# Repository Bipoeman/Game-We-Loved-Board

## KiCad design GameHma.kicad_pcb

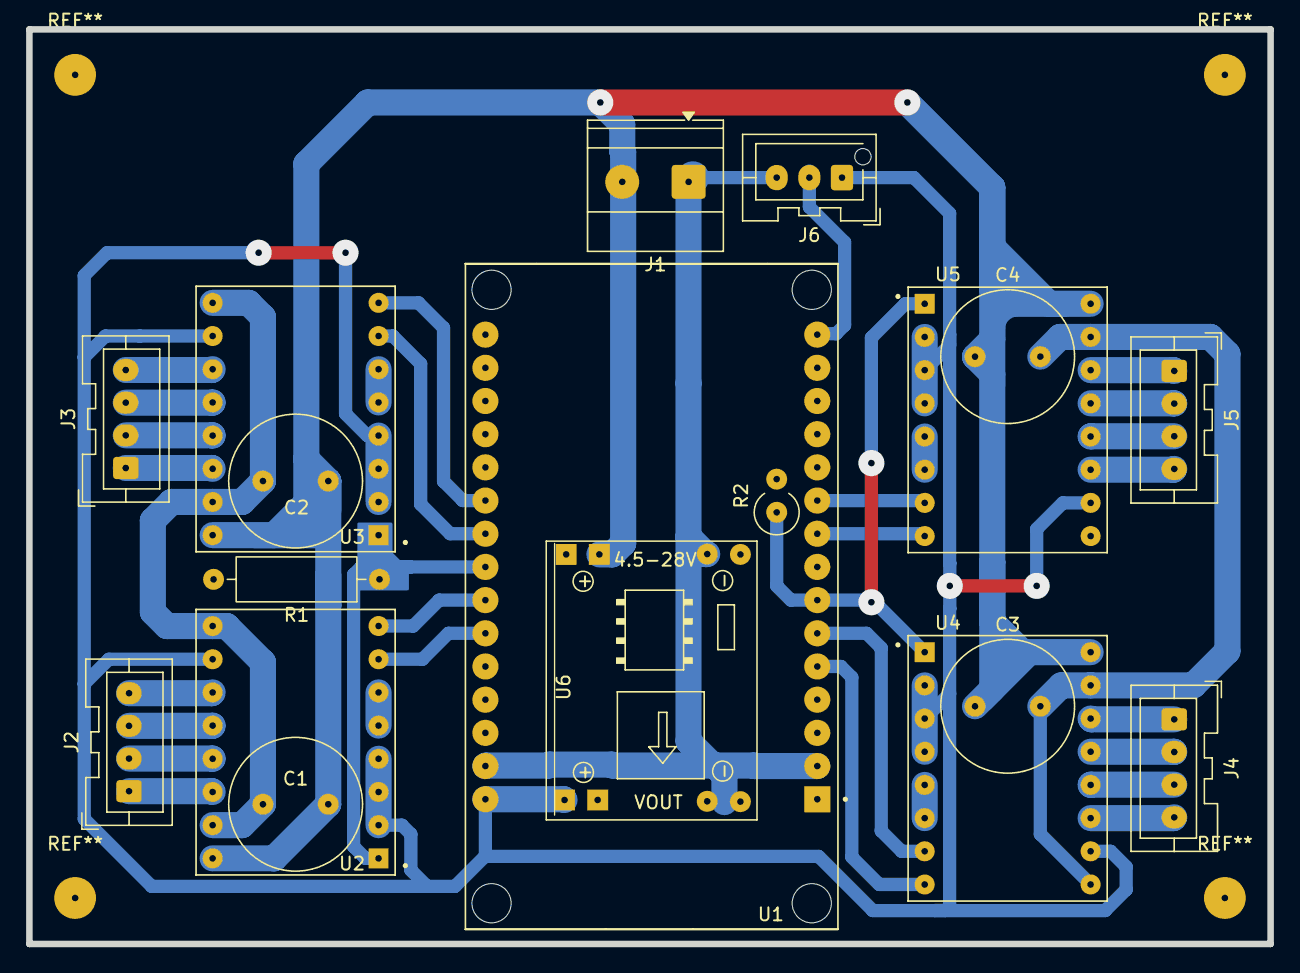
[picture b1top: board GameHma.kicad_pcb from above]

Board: 2 copper layers, 95.0 x 70.0 mm, 18 parts (0 on the bottom side), 34 nets.

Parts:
C1, C2, C3, C4: 100u; C_Radial_D10.0mm_H16.0mm_P5.00mm
J1: Screw_Terminal_01x02; TerminalBlock_Phoenix_MKDS-1,5-2-5.08_1x02_P5.08mm_Horizont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
J2, J3, J4, J5: Motor_Terminal_01x04; JST_XA_B04B-XASK-1_1x04_P2.50mm_Vertical
J6: Conn_01x03; JST_XA_B03B-XASK-1-A_1x03_P2.50mm_Vertical
R1: 10; R_Axial_DIN0309_L9.0mm_D3.2mm_P12.70mm_Horizontal
R2: 10; R_Axial_DIN0309_L9.0mm_D3.2mm_P2.54mm_Vertical
U1: ESP32-DEVKIT-V1; ESP32 Dev Board
U2, U3, U4, U5: A4988 Stepper Driver Module; A4988 Stepper Driver
U6: SRT_MP1584EN; MPT1584EN_Module

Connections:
+V_{DD}: J6.1, U1.30 (VIN), U2.2 (MS1), U2.3 (MS2), U2.4 (MS3), U2.10 (VDD), U3.2 (MS1), U3.3 (MS2), U3.4 (MS3), U3.10 (VDD), U4.2 (MS1), U4.3 (MS2), U4.4 (MS3), U4.10 (VDD), U5.2 (MS1), U5.3 (MS2), U5.4 (MS3), U5.10 (VDD), U6.3 (Output+)
+V_{batt}: C1.1, C2.1, C3.1, C4.1, J1.2, U2.16 (VMOT), U3.16 (VMOT), U4.16 (VMOT), U5.16 (VMOT), U6.1 (Input+)
DIR_1: U1.21 (D32), U3.8 (DIR)
DIR_2: U1.24 (D26), U2.8 (DIR)
DIR_3: U1.5 (D4), U4.8 (DIR)
DIR_4: U1.9 (D18), U5.8 (DIR)
GND: C1.2, C2.2, C3.2, C4.2, J1.1, J6.3, R1.2, R2.2, U1.2 (GND), U1.29 (GND), U2.9 (GND), U2.15 (GND), U3.9 (GND), U3.15 (GND), U4.9 (GND), U4.15 (GND), U5.9 (GND), U5.15 (GND), U6.2 (Input-), U6.4 (Output-)
LASER_TRIGGER: J6.2, U1.15 (D23)
MOTOR_EN_LEFT: R1.1, U1.23 (D25), U2.1 (~ENABLE), U3.1 (~ENABLE)
MOTOR_EN_RIGHT: R2.1, U1.7 (TX2), U4.1 (~ENABLE), U5.1 (~ENABLE)
unnamed: J2.1, U2.14 (2B)
unnamed: J2.2, U2.13 (2A)
unnamed: J2.3, U2.12 (1A)
unnamed: J2.4, U2.11 (1B)
unnamed: J3.1, U3.14 (2B)
unnamed: J3.2, U3.13 (2A)
unnamed: J3.3, U3.12 (1A)
unnamed: J3.4, U3.11 (1B)
unnamed: J4.1, U4.14 (2B)
unnamed: J4.2, U4.13 (2A)
unnamed: J4.3, U4.12 (1A)
unnamed: J4.4, U4.11 (1B)
unnamed: J5.1, U5.14 (2B)
unnamed: J5.2, U5.13 (2A)
unnamed: J5.3, U5.12 (1A)
unnamed: J5.4, U5.11 (1B)
unnamed: U2.5 (~RESET), U2.6 (~SLEEP)
unnamed: U3.5 (~RESET), U3.6 (~SLEEP)
unnamed: U4.5 (~RESET), U4.6 (~SLEEP)
unnamed: U5.5 (~RESET), U5.6 (~SLEEP)
STEP_1: U1.22 (D33), U3.7 (STEP)
STEP_2: U1.25 (D27), U2.7 (STEP)
STEP_3: U1.6 (RX2), U4.7 (STEP)
STEP_4: U1.10 (D19), U5.7 (STEP)

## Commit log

2025-08-08 initial project and add logo
2025-08-09 add symbol ESP32 DEVKIT V1 and A4988 STEPPER MOTOR
2025-08-09 connect 3V3 and GND pin
2025-08-09 add more 3 steper motor, connect 3V3 and GND pins
2025-08-09 add Battery terminal and Motor terminal, connect Vin and edit VMOT in U4 because it wrong connetion
2025-08-09 edit VMOT U3 because its not connect, connect STEP and DIR pins of each A4988, add Label Vcc and Ground, edit wires color(Red is Vcc, Black is GND, Red-Orange is 3V3, Blue is STEP, Green is DIR
2025-08-09 move logo
2025-08-09 add new motor termina(1x4) then connected wires to it
2025-08-09 edit wires color of moters
2025-08-09 edit motor terminal wires
2025-08-09 fix wire error, add capcitor 100u to each a4988
2025-08-09 rearrange
2025-08-09 example of how it's done done done
2025-08-09 rearrange all wires and all components
2025-08-09 nothing
2025-08-09 create and build SRT_MP1584EN symbol library, add MP1584 in schematic
2025-08-09 Organize and add names
2025-08-09 add foot print to all companents
2025-08-09 build PCB from Schematic
2025-08-10 swap pin 1A and 1B in each MP1584, organized PCB and initial rout
2025-08-10 edit schematic GPIO pin in ESP32, Rout a PCB lines
2025-08-10 Add log, Finish PCB rout line
2025-08-10 add 3d model
2025-08-10 Dril a hole M3
2025-08-10 config footprint 3D Model
2025-08-10 fix pin MP1584 footprint
2025-08-10 edit wire in U2 pin Vbatt at PCB editor
2025-08-10 edit wire in U2 pin VDD at PCB editor
2025-08-10 add connector for gun
2025-08-10 add gitignore
2025-08-11 PCB done
2025-08-11 edit hole size for etching
2025-08-15 ground plane for dry film
2025-08-17 Fab prepare
2025-08-17 Quite Ready for JLC
2025-09-07 PCB Fabricate
2025-09-19 edit for direct motor
2026-01-06 KiCad update: 2026-01-06 14:31:30
2026-01-06 KiCad update: 2026-01-06 14:34:17
2026-01-06 KiCad update: 2026-01-06 14:36:35
